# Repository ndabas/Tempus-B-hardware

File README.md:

# Tempus B - GPS Clock

This project is a simple desk clock, synchronized to GPS using an on-board or external GPS receiver.

An ATtiny85 microcontroller runs the operation. Six 7-segment digits (in two 3-digit modules with colons) display the time. The display is controlled via an HT16K33 driver over I2C.

## Current Status

The hardware works. I got the boards fabricated by Elecrow, and everything looks good. I'm working on finalizing the software (which is currently written using Arduino.)

## Design

I used an ATtiny85 as a challenge in using the smallest possible (both in terms of memory and I/O pins) microcontroller while still maintining a high level of accuracy. The ATtiny has 8K of flash and 512 bytes of RAM. The design uses 5 I/O pins to receive serial data and PPS from the GPS module, and also control the display over I2C. The display controller also has keyscan built-in, so I use that to read two buttons for human interaction. There's also a little piezo speaker on board for beeps and boops.

I've used a mix of through-hole and SMD parts, partly to make construction easy and partly because I used whatever I had lying around.

The board has a footprint for the Global Top PA6H GPS module, as used in the [Adafruit Ultimate GPS v3](https://www.adafruit.com/product/746). There's a pin header as well to plug in the Adafruit board instead; you could use your own GPS module by connecting up the pins there. The board can work with 5V or 3.3V logic. All that's needed is the TX  and the PPS from the GPS module.

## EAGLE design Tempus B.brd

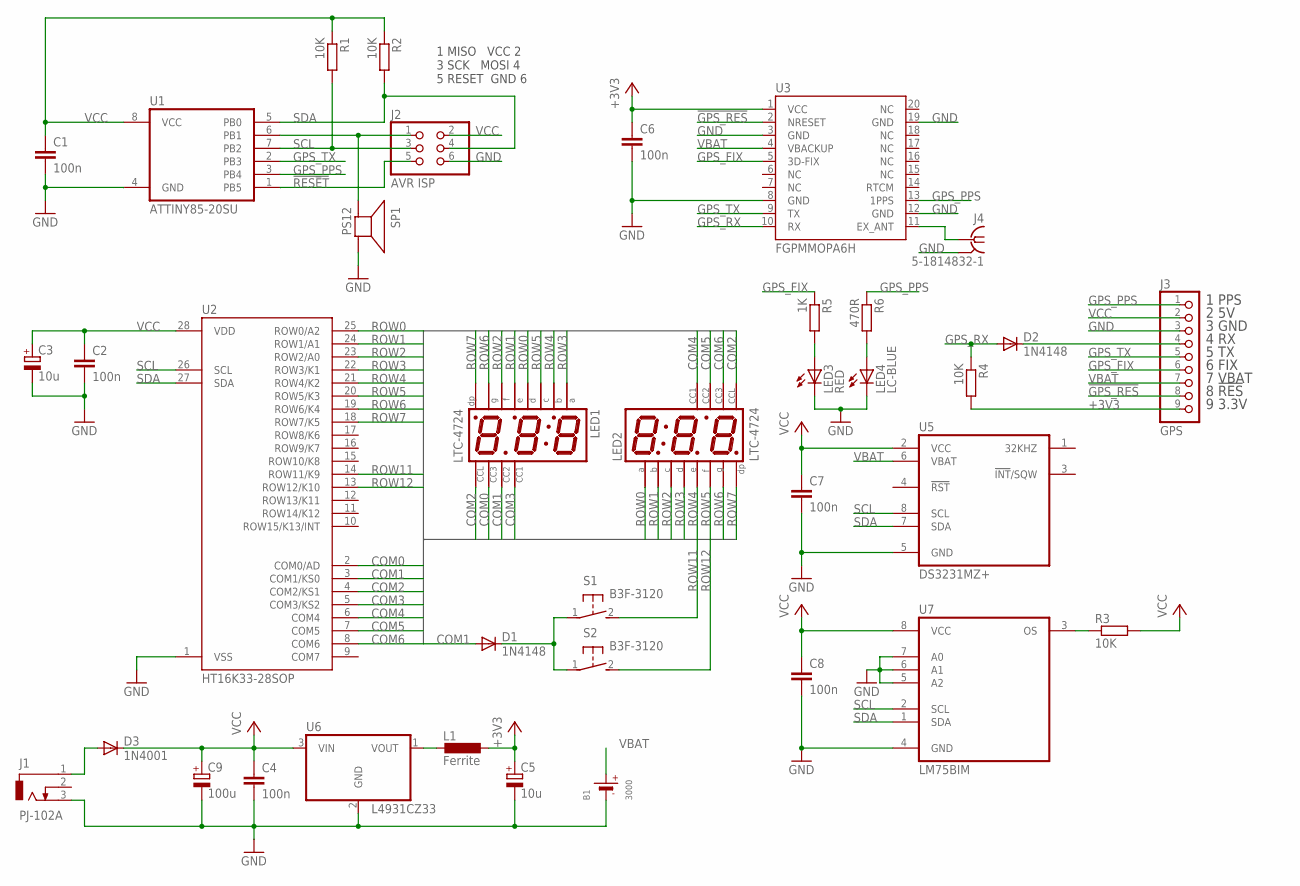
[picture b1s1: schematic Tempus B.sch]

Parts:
B1: 3000; CR1220
C1, C2, C4, C6, C7, C8: 100n; C1206
C3, C5: 10u; E2-5
C9: 100u; E2-5
D1, D2: 1N4148; DO35-10
D3: 1N4001; DO41-10
J1: PJ-102A; DCJACK-2.0MM
J2: AVR ISP; 2X03
J3: GPS; 1X09
J4: 5-1814832-1; SMA-TH-ST
L1: Ferrite; L3216C
LED1, LED2: LTC-4724; DIL15-LTC-4724
LED3: RED; CHIPLED_1206
LED4: LC-BLUE; CHIPLED_1206
R1, R2, R3, R4: 10K; R1206
R5: 1K; R1206
R6: 470R; R1206
S1, S2: B3F-3120; B3F-31XX
SP1: PS12
U1: ATTINY85-20SU; SO08-EIAJ
U2: HT16K33-28SOP; SO28W
U3: FGPMMOPA6H
U5: DS3231MZ+; SO08
U6: L4931CZ33; TO92-LINE
U7: LM75BIM; SO08

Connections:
!GPS_RES: J3.8, U3.2 (NRESET)
!RESET: J2.5, U1.1 (PB5)
+3V3: C5.+, C6.1, J3.9, L1.1, R4.2, U3.1 (VCC)
COM0: LED1.7 (CC3), U2.2 (COM0/AD)
COM1: D1.A, LED1.5 (CC2), U2.3 (COM1/KS0)
COM2: LED1.14 (CCL), LED2.14 (CCL), U2.4 (COM2/KS1)
COM3: LED1.1 (CC1), U2.5 (COM3/KS2)
COM4: LED2.1 (CC1), U2.6 (COM4)
COM5: LED2.5 (CC2), U2.7 (COM5)
COM6: LED2.7 (CC3), U2.8 (COM6)
GND: B1.-, C1.2, C2.2, C3.-, C4.2, C5.-, C6.2, C7.2, C8.2, C9.-, J1.3, J2.6, J3.3, J4.2, J4.3 (2), J4.4 (2), J4.5 (2), LED3.C, LED4.C, SP1.P$2 (-), U1.4 (GND), U2.1 (VSS), U3.3 (GND), U3.8 (GND), U3.12 (GND), U3.19 (GND), U5.5 (GND), U6.2 (GND), U7.4 (GND), U7.5 (A2), U7.6 (A1), U7.7 (A0)
GPS_FIX: J3.6, R5.1, U3.5 (3D-FIX)
GPS_PPS: J3.1, R6.1, U1.3 (PB4), U3.13 (1PPS)
GPS_RX: D2.A, R4.1, U3.10 (RX)
GPS_TX: J3.5, U1.2 (PB3), U3.9 (TX)
unnamed: D1.C, S1.1, S2.1
unnamed: D3.A, J1.1
unnamed: J2.1, SP1.P$1 (+), U1.6 (PB1)
unnamed: LED3.A, R5.2
unnamed: J4.1, U3.11 (EX_ANT)
unnamed: R3.1, U7.3 (OS)
unnamed: L1.2, U6.1 (VOUT)
unnamed: LED4.A, R6.2
unnamed: D2.C, J3.4
ROW0: LED1.4 (D), LED2.12 (A), U2.25 (ROW0/A2)
ROW1: LED1.2 (E), LED2.11 (B), U2.24 (ROW1/A1)
ROW2: LED1.15 (F), LED2.3 (C), U2.23 (ROW2/A0)
ROW3: LED1.12 (A), LED2.4 (D), U2.22 (ROW3/K1)
ROW4: LED1.11 (B), LED2.2 (E), U2.21 (ROW4/K2)
ROW5: LED1.3 (C), LED2.15 (F), U2.20 (ROW5/K3)
ROW6: LED1.8 (G), LED2.8 (G), U2.19 (ROW6/K4)
ROW7: LED1.6 (DP), LED2.6 (DP), U2.18 (ROW7/K5)
ROW11: S1.2 (S), U2.14 (ROW11/K9)
ROW12: S2.2 (S), U2.13 (ROW12/K10)
SCL: J2.3, R1.2, U1.7 (PB2), U2.26 (SCL), U5.8 (SCL), U7.2 (SCL)
SDA: J2.4, R2.2, U1.5 (PB0), U2.27 (SDA), U5.7 (SDA), U7.1 (SDA)
VBAT: B1.+$1 (+), J3.7, U3.4 (VBACKUP), U5.6 (VBAT)
VCC: C1.1, C2.1, C3.+, C4.1, C7.1, C8.1, C9.+, D3.C, J2.2, J3.2, R1.1, R2.1, R3.2, U1.8 (VCC), U2.28 (VDD), U5.2 (VCC), U6.3 (VIN), U7.8 (VCC)

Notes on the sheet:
1 MISO VCC 2 3 SCK MOSI 4 5 RESET GND 6
1 PPS 2 5V 3 GND 4 RX 5 TX 6 FIX 7 VBAT 8 !RES 9 3.3V

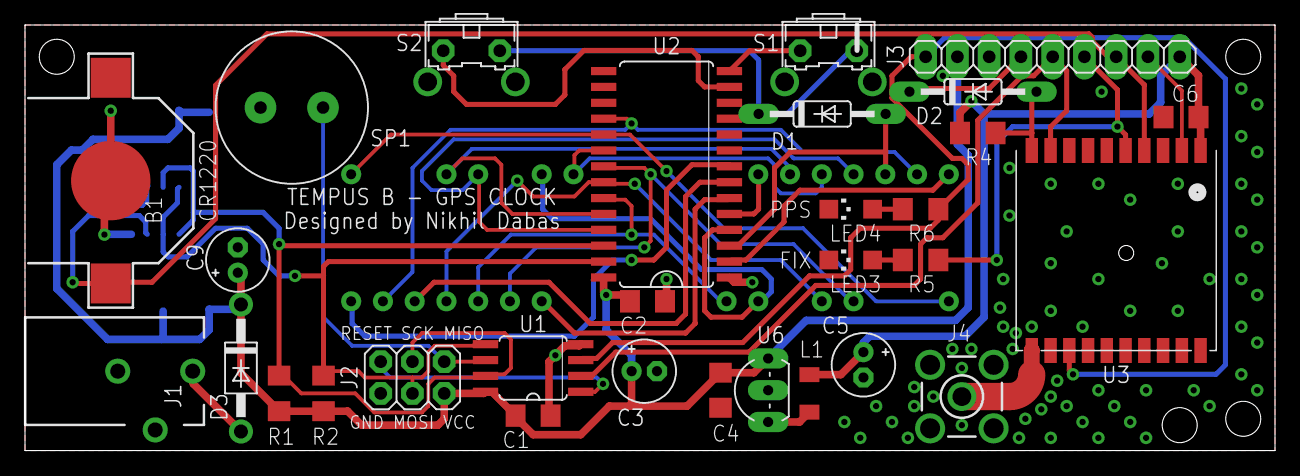
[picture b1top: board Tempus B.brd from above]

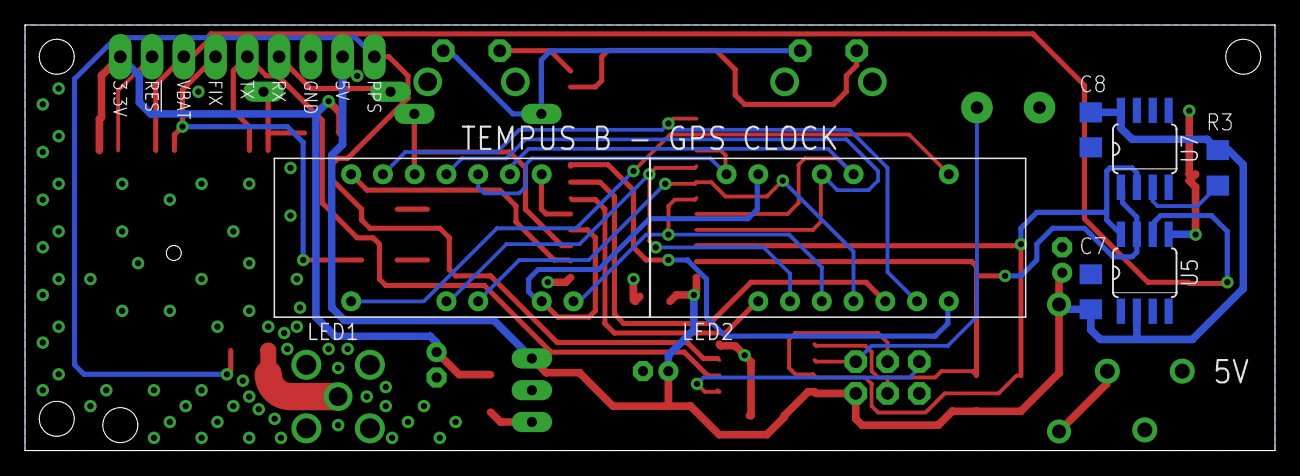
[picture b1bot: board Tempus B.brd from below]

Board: 2 copper layers, 100.0 x 34.0 mm, 37 parts (7 on the bottom side), 38 nets.

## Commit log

2017-08-21 PCBs sent for fabrication!
2017-10-07 Tweaking LED resistor values
    After testing with the LEDs I ordered, it turns out we need a really
    tiny current (0.5mA to 1mA) for the LEDs.
2017-10-07 Add README
2017-10-07 Fix spaces in image URLs
